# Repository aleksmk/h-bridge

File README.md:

This is a high-power-minded H-Bridge driver for driving DC motors. It was successfully tested on a 100V/4A DC motor.

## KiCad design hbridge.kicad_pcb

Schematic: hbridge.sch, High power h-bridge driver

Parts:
C1: 68u/400V
C2, C3, C7: 1u
C4, C8, C9, C10, C12, C13: 100n
C5: 1n
C11: 27nF/250V
F1, F2: 5A
K1: I SENSE
L1, L2: CHOKE
P1: 15V_IR
P2: MOTOR
P3: 12V L
P4: 12V R
P5: M VCC
P6: IR_VDD
P7: CONN_5
P8: TP3
P9: TP4
P10: TP1
P11: TP2
Q1, Q2, Q3, Q4: STW15NB50
R1, R2, R3, R4: 4R3
R5, R6, R7, R8: 4k7
R9, R10, R11, R12: 330
R13, R14: 0
TR1, TR2, TR3, TR4: BIDI Transil
TR5: TVS 150V
U1, U2: IR2110S
U3: ACS706ELC-05C; SO8
U4: 74HC14
U5, U7, U8, U9: EL817
U6: 7408

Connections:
+5V: C8.1, C9.1, C12.1, C13.1, P6.1, R5.1, R6.1, R7.1, R8.1, U1.11 (VDD), U2.11 (VDD), U4.14 (VCC), U6.14 (Vcc)
GNDPWR: P7.1, U5.2 (K), U7.2 (K), U8.2 (K), U9.2 (K)
IR2110_VCC: C4.1, C10.1, P1.1, U1.3 (VCC), U2.3 (VCC)
L_HIGH: P7.2, R9.1
L_HIN: U1.12 (HIN), U4.8, U6.1
L_LIN: U1.14 (LIN), U4.6, U6.2
L_LOW: P7.3, R10.1
L_SD: R13.1, U1.13 (SD), U6.3
unnamed: R3.1, U1.1 (LO)
unnamed: R1.1, U1.8 (HO)
unnamed: Q2.G, R2.1, TR2.2
unnamed: Q4.G, R4.1, TR4.2
unnamed: Q3.G, R3.2, TR3.2
unnamed: Q1.G, R1.2, TR1.2
unnamed: R9.2, U5.1 (A)
unnamed: C7.1, K1.1, U3.8 (VCC)
unnamed: K1.2 (PM), U3.7 (VIout)
unnamed: C5.1, U3.6 (DNC)
unnamed: C2.1, P3.1, U1.7 (VB)
unnamed: R12.2, U9.1 (A)
unnamed: Q3.S, Q4.S, TR3.1, TR4.1, U3.1 (IP+), U3.2 (IP+)
unnamed: F2.1, Q2.D
unnamed: C11.2, L2.1, P2.2 (PM), P11.1, TR5.2
unnamed: C11.1, L1.2, P2.1, P10.1, TR5.1
unnamed: F1.1, Q1.D
unnamed: R8.2, U4.1, U9.4 (C)
unnamed: R7.2, U4.3, U8.4 (C)
unnamed: R6.2, U4.5, U7.4 (C)
unnamed: R5.2, U4.9, U5.4 (C)
unnamed: R10.2, U7.1 (A)
unnamed: R11.2, U8.1 (A)
unnamed: C3.1, P4.1, U2.7 (VB)
unnamed: R4.2, U2.1 (LO)
unnamed: R2.2, U2.8 (HO)
unnamed: C5.2, C7.2, K1.3, U3.5 (GND)
unnamed: C2.2, L1.1, P3.2 (PM), P8.1, Q1.S, Q3.D, TR1.1, U1.6 (VS)
unnamed: C3.2, L2.2, P4.2 (PM), P9.1, Q2.S, Q4.D, TR2.1, U2.6 (VS)
R_HIGH: P7.4, R11.1
R_HIN: U2.12 (HIN), U4.4, U6.4
R_LIN: U2.14 (LIN), U4.2, U6.5
R_LOW: P7.5, R12.1
R_SD: R14.1, U2.13 (SD), U6.6
Vmot+: C1.1, F1.2, F2.2, P5.1
Vmot-: C1.2, C4.2, C8.2, C9.2, C10.2, C12.2, C13.2, P1.2 (PM), P5.2 (PM), P6.2 (PM), R13.2, R14.2, U1.2 (COM), U1.15 (VSS), U2.2 (COM), U2.15 (VSS), U3.3 (IP-), U3.4 (IP-), U4.7 (GND), U5.3 (E), U6.7 (Gnd), U7.3 (E), U8.3 (E), U9.3 (E)

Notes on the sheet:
Suppression capacitor
TVS
Optional
MOTOR
At motor's end

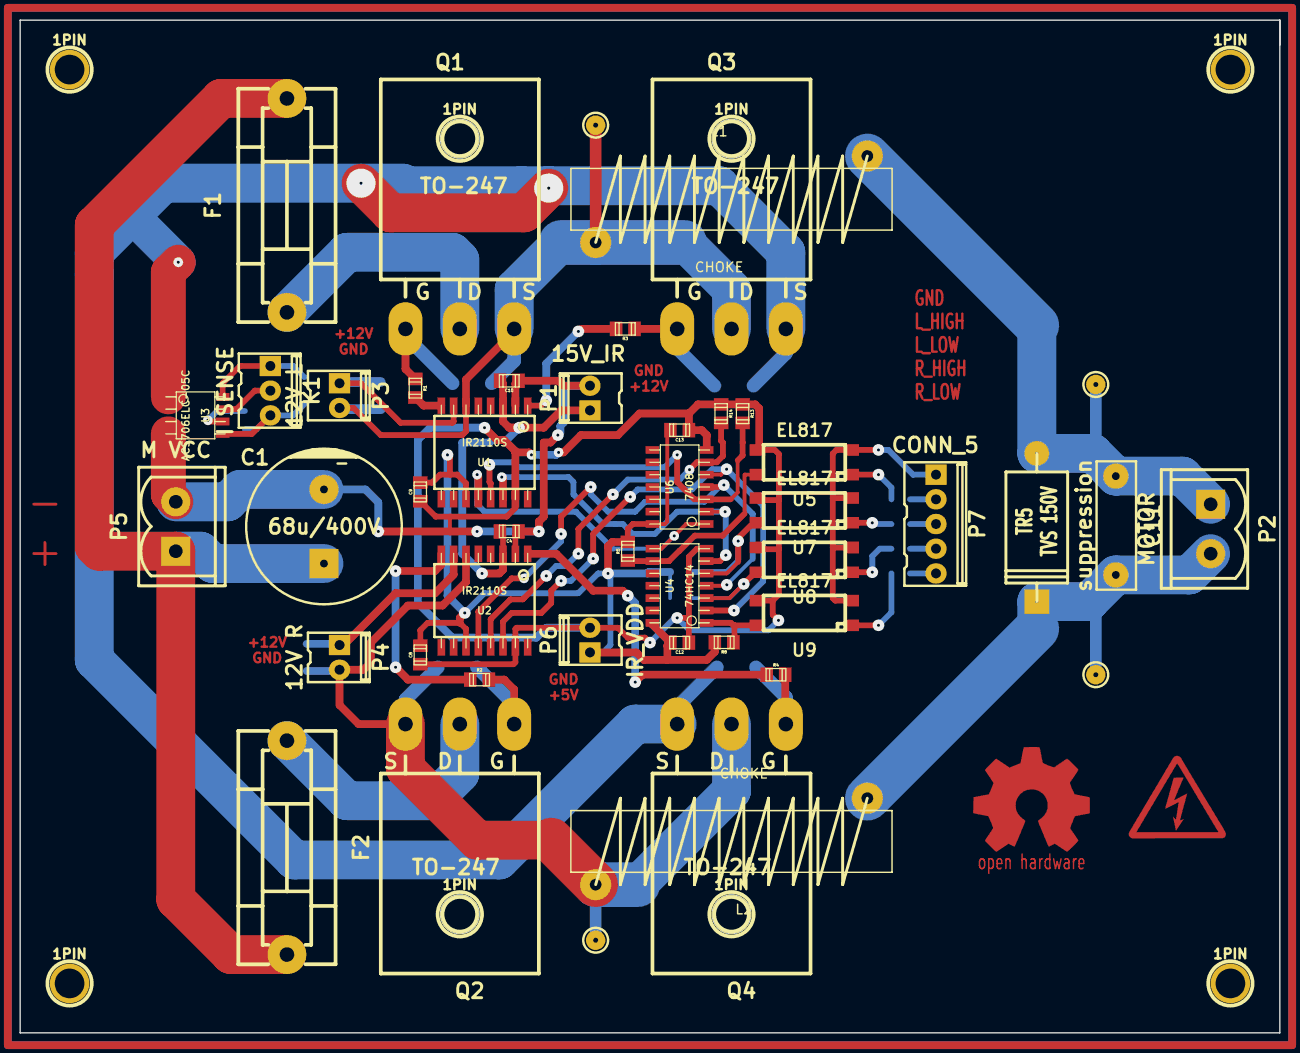
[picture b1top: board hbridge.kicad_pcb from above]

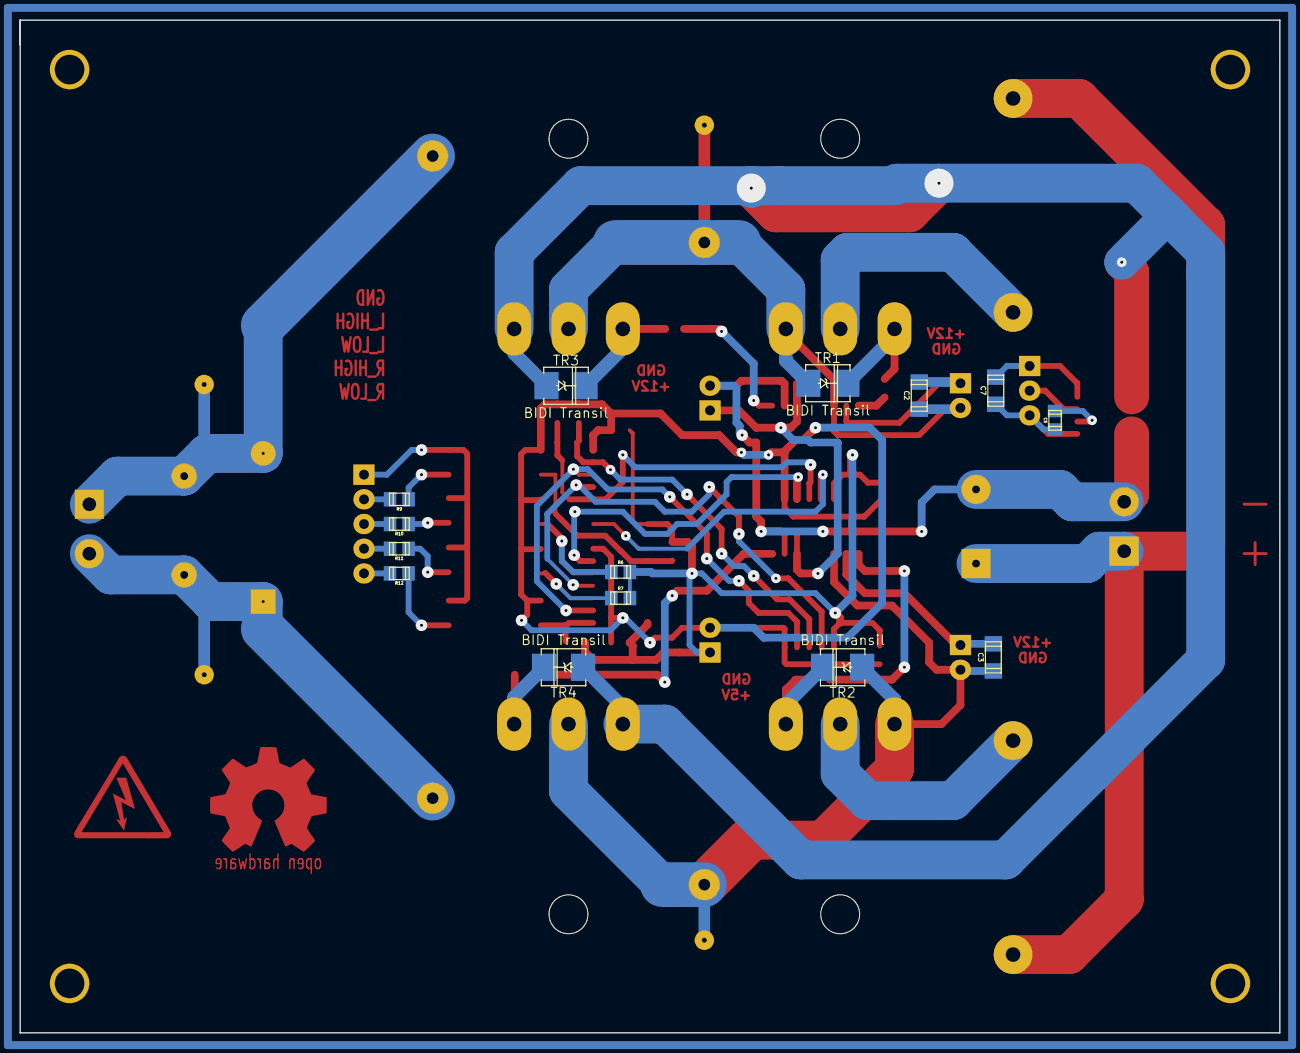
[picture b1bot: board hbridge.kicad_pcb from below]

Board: 2 copper layers, 129.5 x 104.1 mm, 68 parts (14 on the bottom side), 44 nets.

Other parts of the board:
1PIN, 1PIN#2, 1PIN#3, 1PIN#4, 1PIN#5, 1PIN#6, 1PIN#7, 1PIN#8: P***; 1pin

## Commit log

2015-12-07 GPLv2
2015-12-07 Small readme
2015-12-07 PDF and PNG for the schematic
